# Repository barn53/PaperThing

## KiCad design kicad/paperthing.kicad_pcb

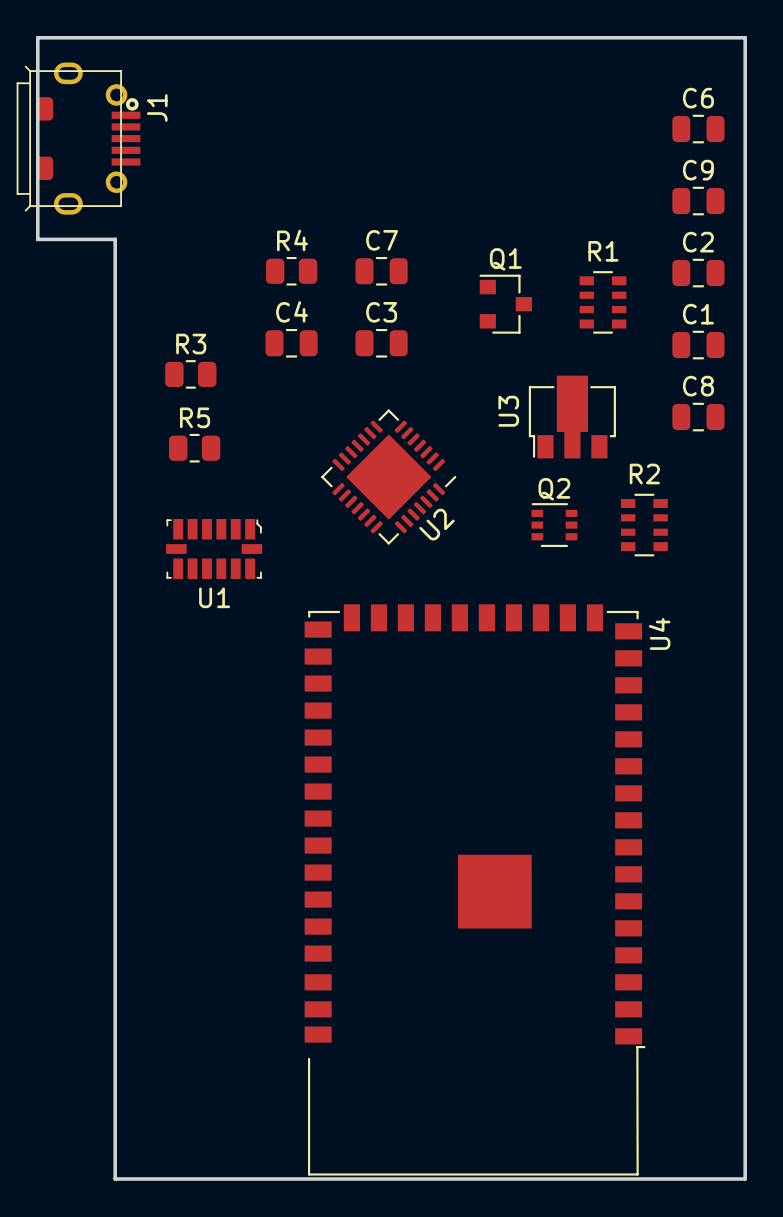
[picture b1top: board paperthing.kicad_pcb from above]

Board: 2 copper layers, 39.3 x 63.4 mm, 20 parts (0 on the bottom side), 16 nets, no tracks yet.

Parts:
C1, C3, C4, C7, C8: 100n; C_0805_2012Metric
C2, C9: 4.7u; C_0805_2012Metric
C6: 1u; C_0805_2012Metric
J1: USB_B_Micro; MicroUSB_through_hole_fixing
Q1: S8050_J3Y; SOT-23
Q2: PMBT2222AYS; SOT-363_SC-70-6
R1, R2: 10k; R_Array_Convex_4x0603
R3: 10; R_0805_2012Metric
R4: 10k; R_0805_2012Metric
R5: 1k; R_0805_2012Metric
U1: ADXL345BCCZ-RL7
U2: CP2102-GMR_NRND; QFN-28-1EP_5x5mm_P0.5mm_EP3.35x3.35mm
U3: BL8565; SOT-89-3
U4: ESP32-S2-WROVER

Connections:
+3V3: C8.1, C9.1, R2.5, R2.8, R4.2, U3.3
/D+: J1.3, U2.4
/D-: J1.2, U2.5
/DTR: Q2.1, R2.2, U2.28
/GPIO0: Q2.6, R2.4
/RTS: Q2.4, R2.3, U2.24
/VDD: C3.1, R1.1, U2.6
/~Reset: C4.1, Q2.3, R2.1
GND: C1.2, C2.2, C3.2, C4.2, C6.2, C7.2, C8.2, C9.2, J1.5, J1.6, Q1.2, U2.3, U2.29, U3.1
unnamed: Q1.1, R4.1, R5.1
unnamed: Q1.3, R3.2
unnamed: Q2.2, R2.6
unnamed: Q2.5, R2.7
unnamed: R1.8, U2.9
unnamed: U4.1, U4.26, U4.42, U4.43
VBUS: C1.1, C2.1, C6.1, C7.1, J1.1, U2.7, U2.8, U3.2

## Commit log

2021-05-27 a starting point
